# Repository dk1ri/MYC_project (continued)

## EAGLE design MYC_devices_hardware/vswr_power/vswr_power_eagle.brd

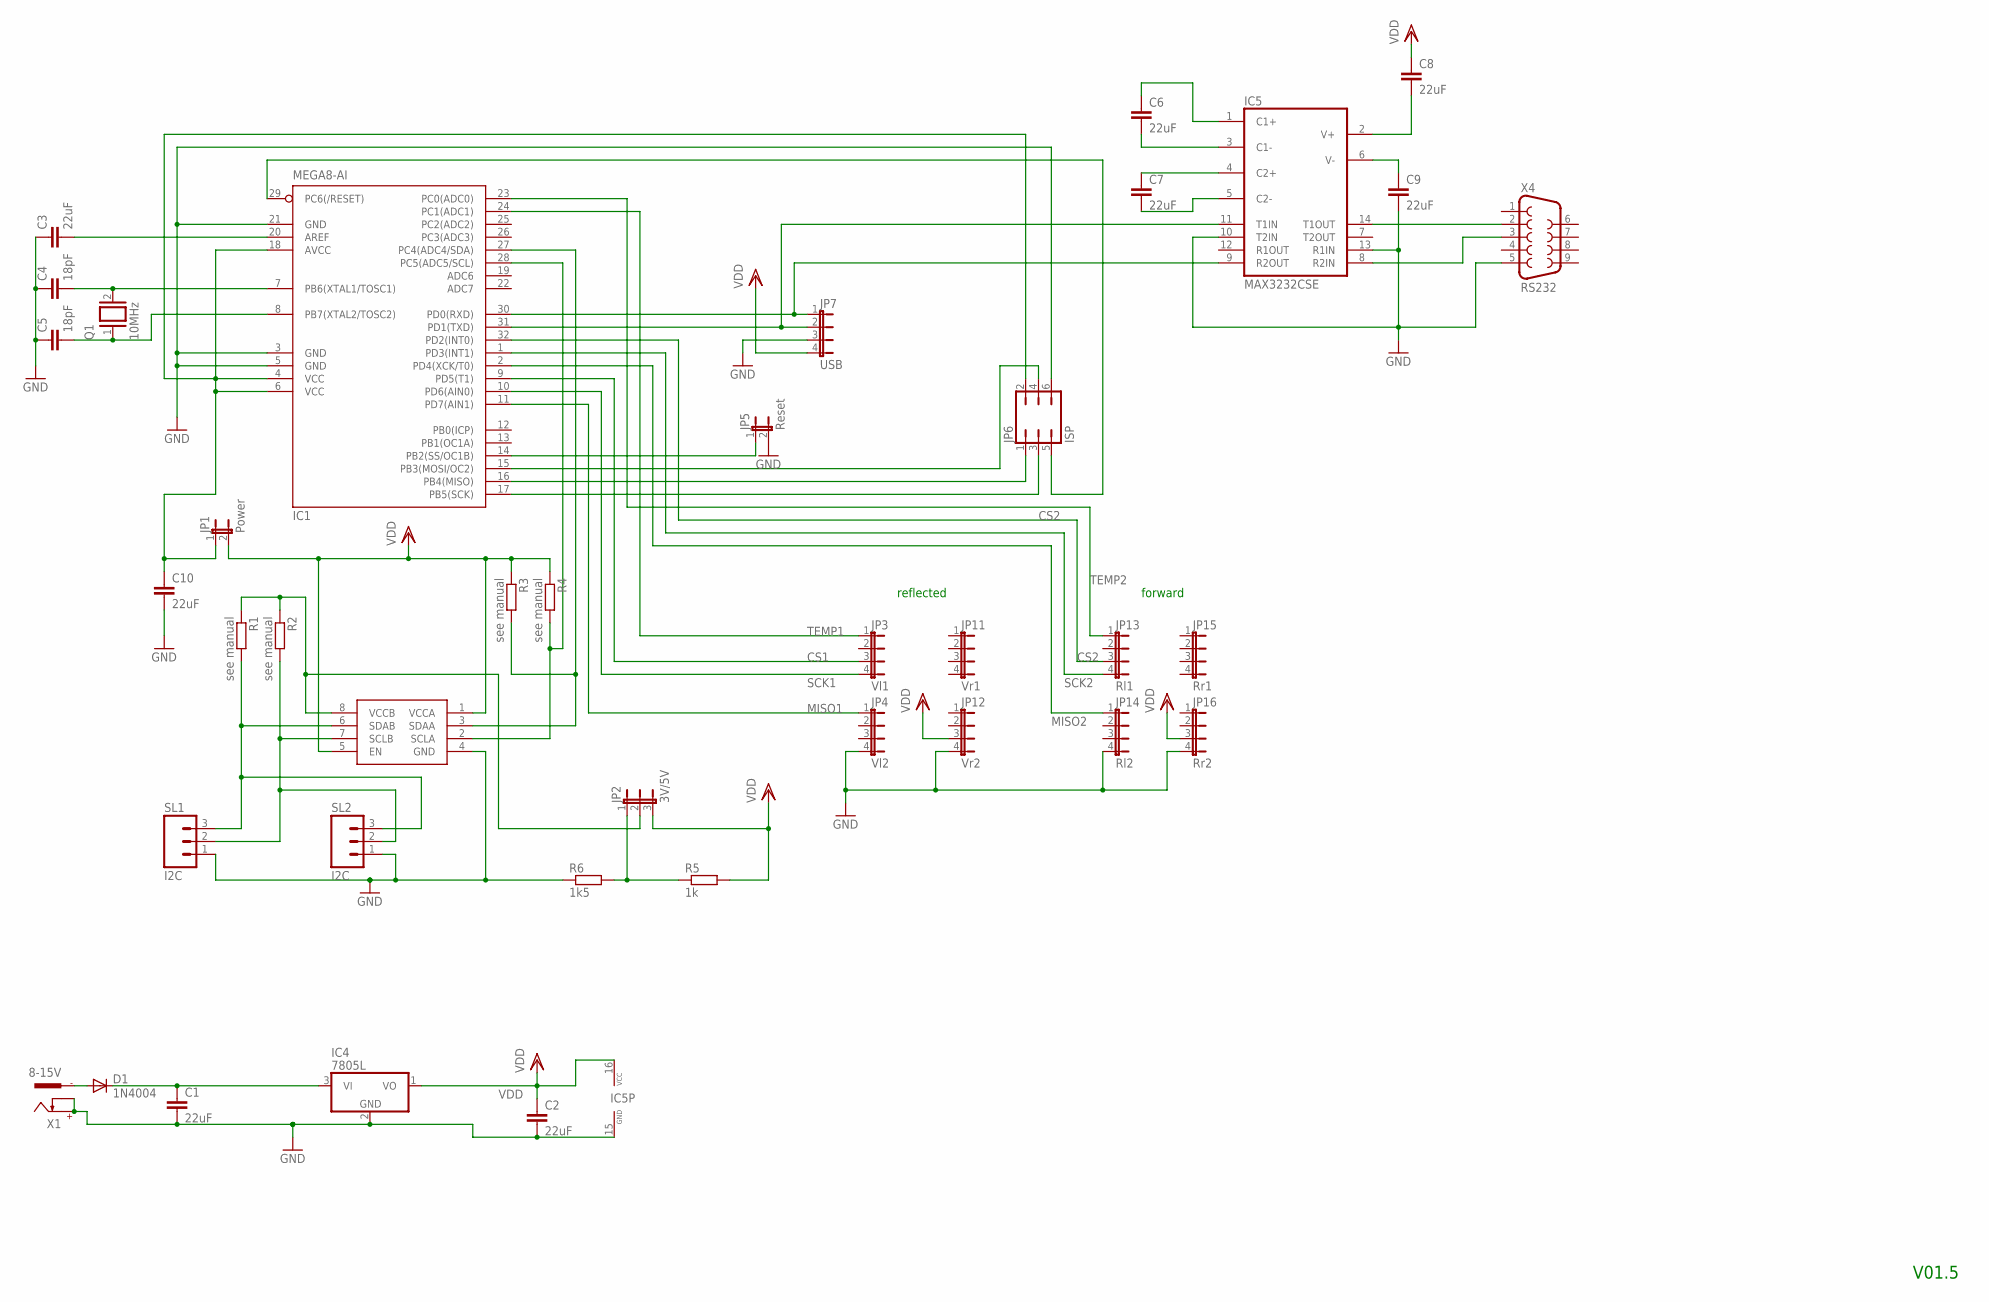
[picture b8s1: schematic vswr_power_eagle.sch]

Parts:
C1, C2, C3, C6, C7, C8, C9, C10: 22uF; C1206
C4, C5: 18pF; C025-025X050
D1: 1N4004; DO41-10
IC1: MEGA8-AI; TQFP32-08
IC3: PCA9517; SO-08
IC4: 7805L; TO92
IC5: MAX3232CSE; SO16
JP1: Power; JP1
JP2: 3V/5V; JP2
JP3: Vl1; JP4
JP4: Vl2; JP4
JP5: Reset; JP1
JP6: ISP; JP3Q
JP7: USB; JP4
JP11: Vr1; JP4
JP12: Vr2; JP4
JP13: Rl1; JP4
JP14: Rl2; JP4
JP15: Rr1; JP4
JP16: Rr2; JP4
Q1: 10MHz; QS
R1, R2, R3, R4: see manual; R1206
R5: 1k; R1206
R6: 1k5; R1206
SL1, SL2: I2C; 03P
X1: 8-15V; 737992-5
X4: RS232; F09H

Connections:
CS1: IC1.9 (PD5(T1)), JP3.3
CS2: IC1.32 (PD2(INT0)), JP13.3
GND: C1.2, C2.2, C3.1, C4.1, C5.1, C9.2, C10.2, IC1.3 (GND), IC1.5 (GND), IC1.21 (GND), IC3.4 (GND), IC4.2 (GND), IC5.10 (T2IN), IC5.13 (R1IN), IC5.15 (GND), JP4.4, JP5.2, JP6.6, JP7.3, JP12.4, JP14.4, JP16.4, R6.1, SL1.1, SL2.1, X1.+, X1.K, X4.5
MISO1: IC1.11 (PD7(AIN1)), JP4.1
MISO2: IC1.2 (PD4(XCK/T0)), JP14.1
unnamed: IC3.6 (SDAB), R1.2, SL1.3, SL2.3
unnamed: IC1.15 (PB3(MOSI/OC2)), JP6.4
unnamed: C1.1, D1.C, IC4.3 (VI)
unnamed: IC3.8 (VCCB), JP2.2, R1.1, R2.1
unnamed: IC1.27 (PC4(ADC4/SDA)), IC3.3 (SDAA), R3.2
unnamed: JP2.1, R5.1, R6.2
unnamed: IC1.28 (PC5(ADC5/SCL)), IC3.2 (SCLA), R4.2
unnamed: IC1.17 (PB5(SCK)), JP6.3
unnamed: IC1.31 (PD1(TXD)), IC5.11 (T1IN), JP7.2
unnamed: IC1.14 (PB2(SS/OC1B)), JP5.1
unnamed: IC5.8 (R2IN), X4.3
unnamed: C3.2, IC1.20 (AREF)
unnamed: IC5.14 (T1OUT), X4.2
unnamed: IC1.16 (PB4(MISO)), JP6.1
unnamed: C8.2, IC5.2 (V+)
unnamed: C6.1, IC5.1 (C1+)
unnamed: IC1.29 (PC6(/RESET)), JP6.5
unnamed: C4.2, IC1.7 (PB6(XTAL1/TOSC1)), Q1.2
unnamed: C6.2, IC5.3 (C1-)
unnamed: C7.2, IC5.5 (C2-)
unnamed: IC3.7 (SCLB), R2.2, SL1.2, SL2.2
unnamed: C7.1, IC5.4 (C2+)
unnamed: C9.1, IC5.6 (V-)
unnamed: C10.1, IC1.4 (VCC), IC1.6 (VCC), IC1.18 (AVCC), JP1.1, JP6.2
unnamed: D1.A, X1.-1
unnamed: IC1.30 (PD0(RXD)), IC5.9 (R2OUT), JP7.1
unnamed: C5.2, IC1.8 (PB7(XTAL2/TOSC2)), Q1.1
SCK1: IC1.10 (PD6(AIN0)), JP3.4
SCK2: IC1.1 (PD3(INT1)), JP13.4
TEMP1: IC1.24 (PC1(ADC1)), JP3.1
TEMP2: IC1.23 (PC0(ADC0)), JP13.1
VDD: C2.1, C8.1, IC3.1 (VCCA), IC3.5 (EN), IC4.1 (VO), IC5.16 (VCC), JP1.2, JP2.3, JP7.4, JP12.3, JP16.3, R3.1, R4.1, R5.2

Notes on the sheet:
V01.5
reflected
forward

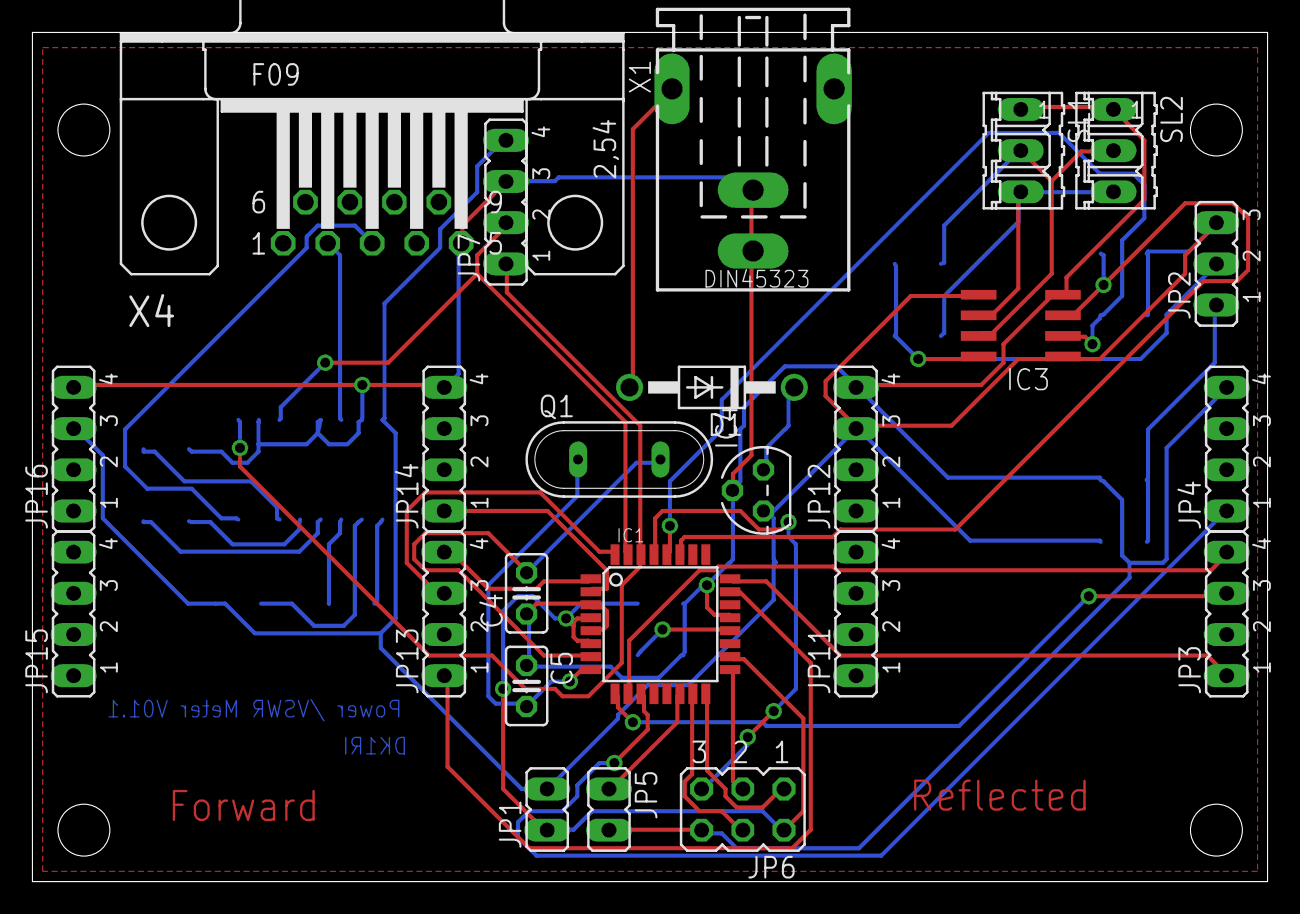
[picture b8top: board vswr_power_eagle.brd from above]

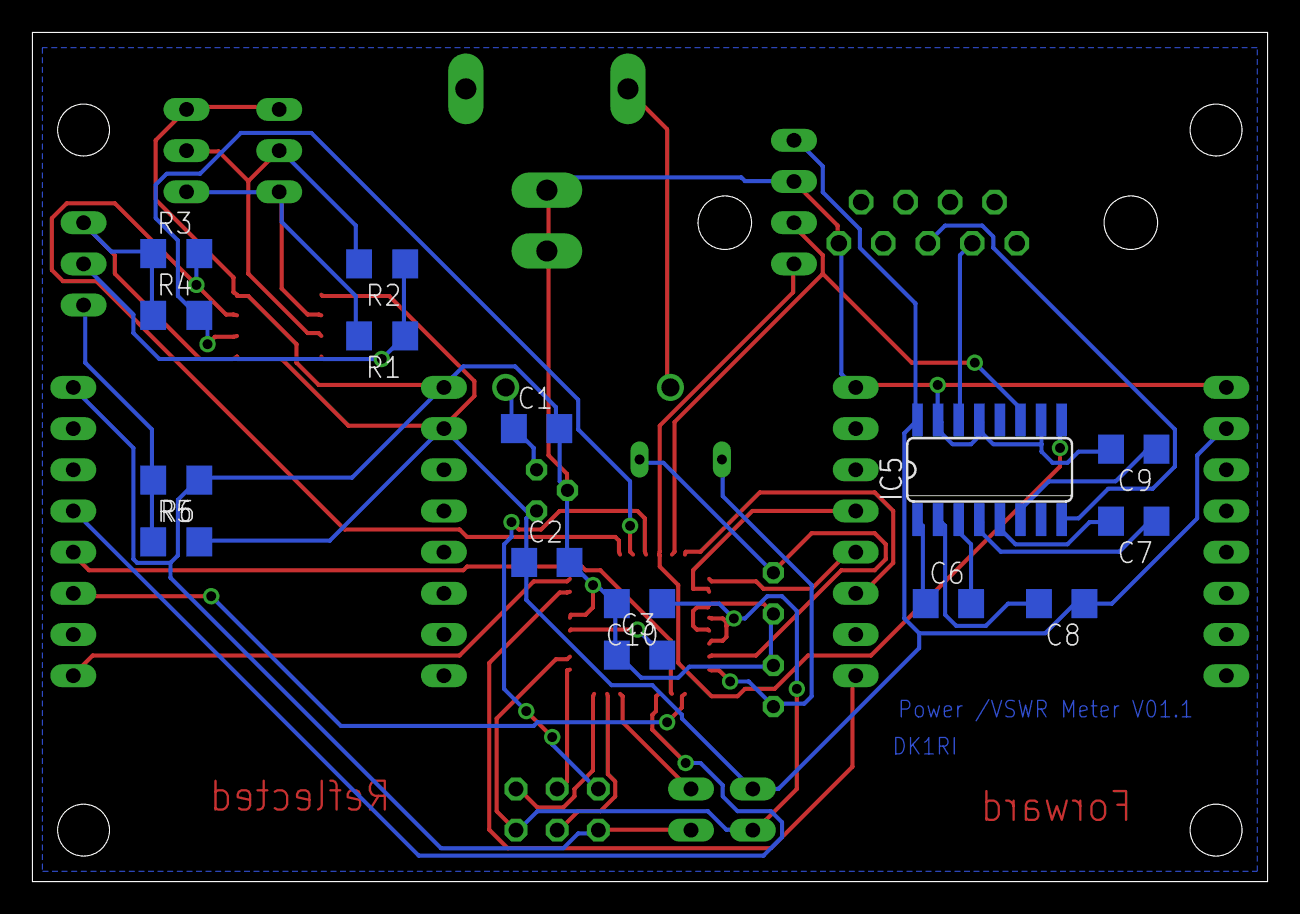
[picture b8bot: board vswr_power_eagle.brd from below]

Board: 2 copper layers, 76.2 x 52.4 mm, 39 parts (15 on the bottom side), 37 nets.

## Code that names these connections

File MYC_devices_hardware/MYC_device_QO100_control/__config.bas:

' additional configs
'202230914

' outputs are set by init_micro
'
' external Temp Sensor (analog Innput)
Temp Alias PinA.0
'
R Alias PinA.1
'
F Alias PinA.2
'
K_Err Alias Pina.3
Config K_err = Input
Set PortA.3
'
' swr of 28V PA (analog Input)
Swr Alias Pina.4
'
'PA1.1
PA1_1 Alias Pina.5
Config PA1_1 = Input
Set PortA.5
'
'PA2.1
PA2_1 Alias Pina.7
Config PA2_1 = Input
Set PortA.7
'
T Alias Pinb.1
Config T = Input
Set Portb.1
'
Led Alias Portc.1
'
Ptt_pin Alias PinC.6
Config Ptt_pin = Input
Set PortC.6
'
NB_WB_pin Alias PinC.7
Config NB_WB_pin = Input
Set PortC.7
'
Config Adc = Single , Prescaler = Auto , Reference = AVCC

' Timerfrequency: 19,5kHz, 51us
' used for LED
Config Timer1 = Timer, Prescale = 1024
Enable Interrupts
Enable Timer1
Declare Sub Timer1_int()
On Timer1 Timer1_int
'
' serial timeout
Config Timer3 = Timer, Prescale = 1024
Enable Timer3
Declare Sub Check_serial_timeout()
On Timer3 Check_serial_timeout
Stop Timer3

' Com2 must be a hardware UART!
' Other than document<tion (old) new firmware has 19200 as Baudrate
Config Com2 = 9600 , Synchrone = 0 , Parity = None , Stopbits = 1 , Databits = 8 , Clockpol = 0
Open "Com2:" For Binary As #2

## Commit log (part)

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2020-10-29 mostly formal changes
2020-11-14 common_1.11 and minor ammendments
2020-11-24 common1.11
2020-11-24 changes for 2 byte commands
2021-02-19 documentazion separated
    -
2021-02-19 document for all ICOM radios
2021-02-20 IC705
2021-02-20 new IC 705 ICOM radio
2021-02-20 missing files __logfile is still missing
2021-03-09 IC705 python added
2021-03-09 new dir for ic7300 python
2021-03-09 V01.4
2021-03-09 2.part
2021-03-09 3rd part
2021-03-09 rest
2021-03-09 one more
2021-03-09 error corrections
2021-03-09 error correction
2021-08-24 new board
2021-09-09 some errors corrected
2021-10-22 Create start
2021-10-22 start
2021-11-24 GPL license file added
2021-11-24 license file added
2021-12-09 error corrections, harmonistation with IC7300 and IC9700
2022-01-13 corrected announcements syntax errors
2022-01-13 corrected announcements syntax errors AND OTHRES
2022-01-13 SOME AMENDEMENTS
2022-03-09 modified des for stacks, other clarifications, some error corrections
2022-07-08 Add files via upload
    description
2022-07-08 1st set
2022-07-08 2nd set
2022-11-11 major changes in structure (simplification
2022-11-11 major changes (other structure)
2022-11-23 some minor mods
2022-11-23 code and structure simplification and correction
2022-11-24 not valid
2022-11-24 not used anymore
2022-12-07 mods of <des>, clarifications
2022-12-28 FIFO dropped, <des> mods
2023-01-25 switches and memory should work
2023-01-25 modified announcement files
2023-02-01 some corrections and clarifications
2023-02-13 GUI and send to device working basically
2023-02-13 some modes
2023-02-13 description /usage
2023-03-04 as_commands added
2023-03-04 new test_b
2023-03-04 ar as checkbox changed; ADMIN, lanuage support
2023-03-04 mods according to actual htdocs
2023-03-12 analyze data from device added; error correction
2023-04-13 CODING added, some corrections
2023-04-13 CODING added
2023-04-13 some minor corrections
2023-04-13 corrections
2023-04-13 CODING added, chapter select modified
2023-05-02 Add files via upload
    common1.12 + error correction
2023-05-02 common1.12 + error correction
2023-05-02 modified common
2023-05-15 slavecore1.12; enhancements, errorcorrection
2023-05-25 description changed: memory and op command
    some additonal rewording and rearranging
2023-06-08 major rework
    now only switches will work
2023-06-09 switch and range commands ok
2023-06-15 error correction /update
2023-06-15 some work on memories, error correction
2023-06-15 clarification with <des>
2023-06-21 most rework done, but still few errors
2023-07-02 correctiion for reveived data
2023-07-02 Create new
2023-07-02 correctio with 240 command
2023-07-03 eeram bug for stri ng solved
2023-07-03 slavecore 1.13
2023-07-04 slave_core 1.13
2023-07-05 slavecore1.13
2023-07-05 slvacore 1.13
2023-07-05 slavecore 1.3
2023-07-15 slavecore 1.13 and announcements changes
2023-07-15 sri wrong data uploaded
2023-07-23 slavecore 1.13 and error correction (Temp)
2023-07-25 mainly error correction
2023-07-27 slavecore 1.13 + announcement changes
2023-08-07 slavecore 1.13 and error correction
2023-09-25 common_1.13 and correcgtrions
2023-09-27 separate board for homematic
2023-09-27 common_1.13
2023-09-27 common_1.13, new homematic board
2023-10-06 common1.13
2023-10-06 Create IO
2023-10-06 for new homematic only
2023-10-14 Create QO100control
    new
2023-10-14 new device
2023-10-19 Airsensor.sch
    new
2023-11-12 some corrections
2023-11-12 new devixe
2023-12-28 error correction (definitions) minor clarification
2023-12-28 new desction
2023-12-28 new design
2024-01-23 major redesign
2024-03-13 error corrected
2024-03-16 AlLL added; some minor error corrrected
2024-03-17 modified GUI
2024-03-18 F0 command noow with 250chars only (due to transfer limitation to webserver)
2024-03-22 Webserver added
2024-03-22 Modification due to webserver, error correction
2024-03-25 more update, bute not ready
2024-04-10 IC705 updated
2024-04-10 still some errors, but workes basically with the webserver
2024-04-10 errors with announcements corrected
2024-04-12 annonce file corrected
2024-04-12 announce file corrected
2024-04-12 announcefile corrected
2024-04-16 announceerror corrected
2024-04-16 translation added
2024-05-03 language added
2024-05-15 added languages edit of color sequence language
2024-06-23 language added; doc error corrected
2024-06-26 some error correction with as and others
2024-06-27 wrong ic number corrected
2024-08-05 more or less complete redesign
2024-08-05 modified description
2024-08-13 error correction language added
2024-09-12 Rules syntax changed
2024-09-16 Ruled syntax changed
2024-10-15 language updated
2024-10-18 correction of translate, error at start corrected
2024-10-18 language added, updated to common_13
2024-10-31 new default translate and error correction
2024-10-31 enhanced annoncement data
2024-11-25 minor clarifications
2024-12-18 Create wireless_interface
2024-12-18 new wireless interface for MYC
2024-12-18 new common for wireless
2024-12-18 common for wireless interface
2024-12-18 Language added and error correction
2024-12-19 Create Feinstaubsensor.bas dust sensor wireless
2024-12-19 dustsensor: wire interface added
2024-12-23 new V / I sensor with wireless interface
2024-12-23 printed board added
2025-01-09 Create ___announcements
2025-01-09 new DATV receiver
2025-01-09 some error corrections
2025-01-10 display error with a commands
2025-01-10 forgotten timeout added
2025-02-02 changes with rules and corresponding of commands
2025-03-09 update versions
2025-03-12 update due to rules device mods
2025-03-15 Announcement rules error
2025-03-16 announcement rules corrected
2025-04-01 some error corrctions
2025-04-22 Mods due to Q rules
2025-06-21 actual state, radio interface not yet working
2025-06-21 update, radio interface not yet working
2025-06-21 reduced board!
2025-08-01 board addd
2025-08-01 dust sensor with wireless interface
2025-08-01 Create __reset
2025-08-03 with wireless interface
2025-08-03 Create __use
2025-08-04 with radio interface
2025-08-04 Create __init
2025-08-04 new with radio interface
2025-08-05 modified board rror correction
2025-08-09 prepared for wireless interface
2025-12-03 new bord and firmware with Lora and 2.4GHz
2025-12-03 Lora and 2.4GHz ok
2025-12-10 some error correction
2025-12-10 ammendments
2025-12-10 0fff4-7 added
2025-12-13 corrctions
2026-01-23 preparation for integration of LD
2026-02-25 CR with LD workong with testfiles
2026-04-18 enhancements and error correction
2026-04-18 major enhancements, LD integrated
2026-06-16 some minor modds
2026-06-19 Add files via upload
    LD added to CR, SK and FU interface updated, error correction
